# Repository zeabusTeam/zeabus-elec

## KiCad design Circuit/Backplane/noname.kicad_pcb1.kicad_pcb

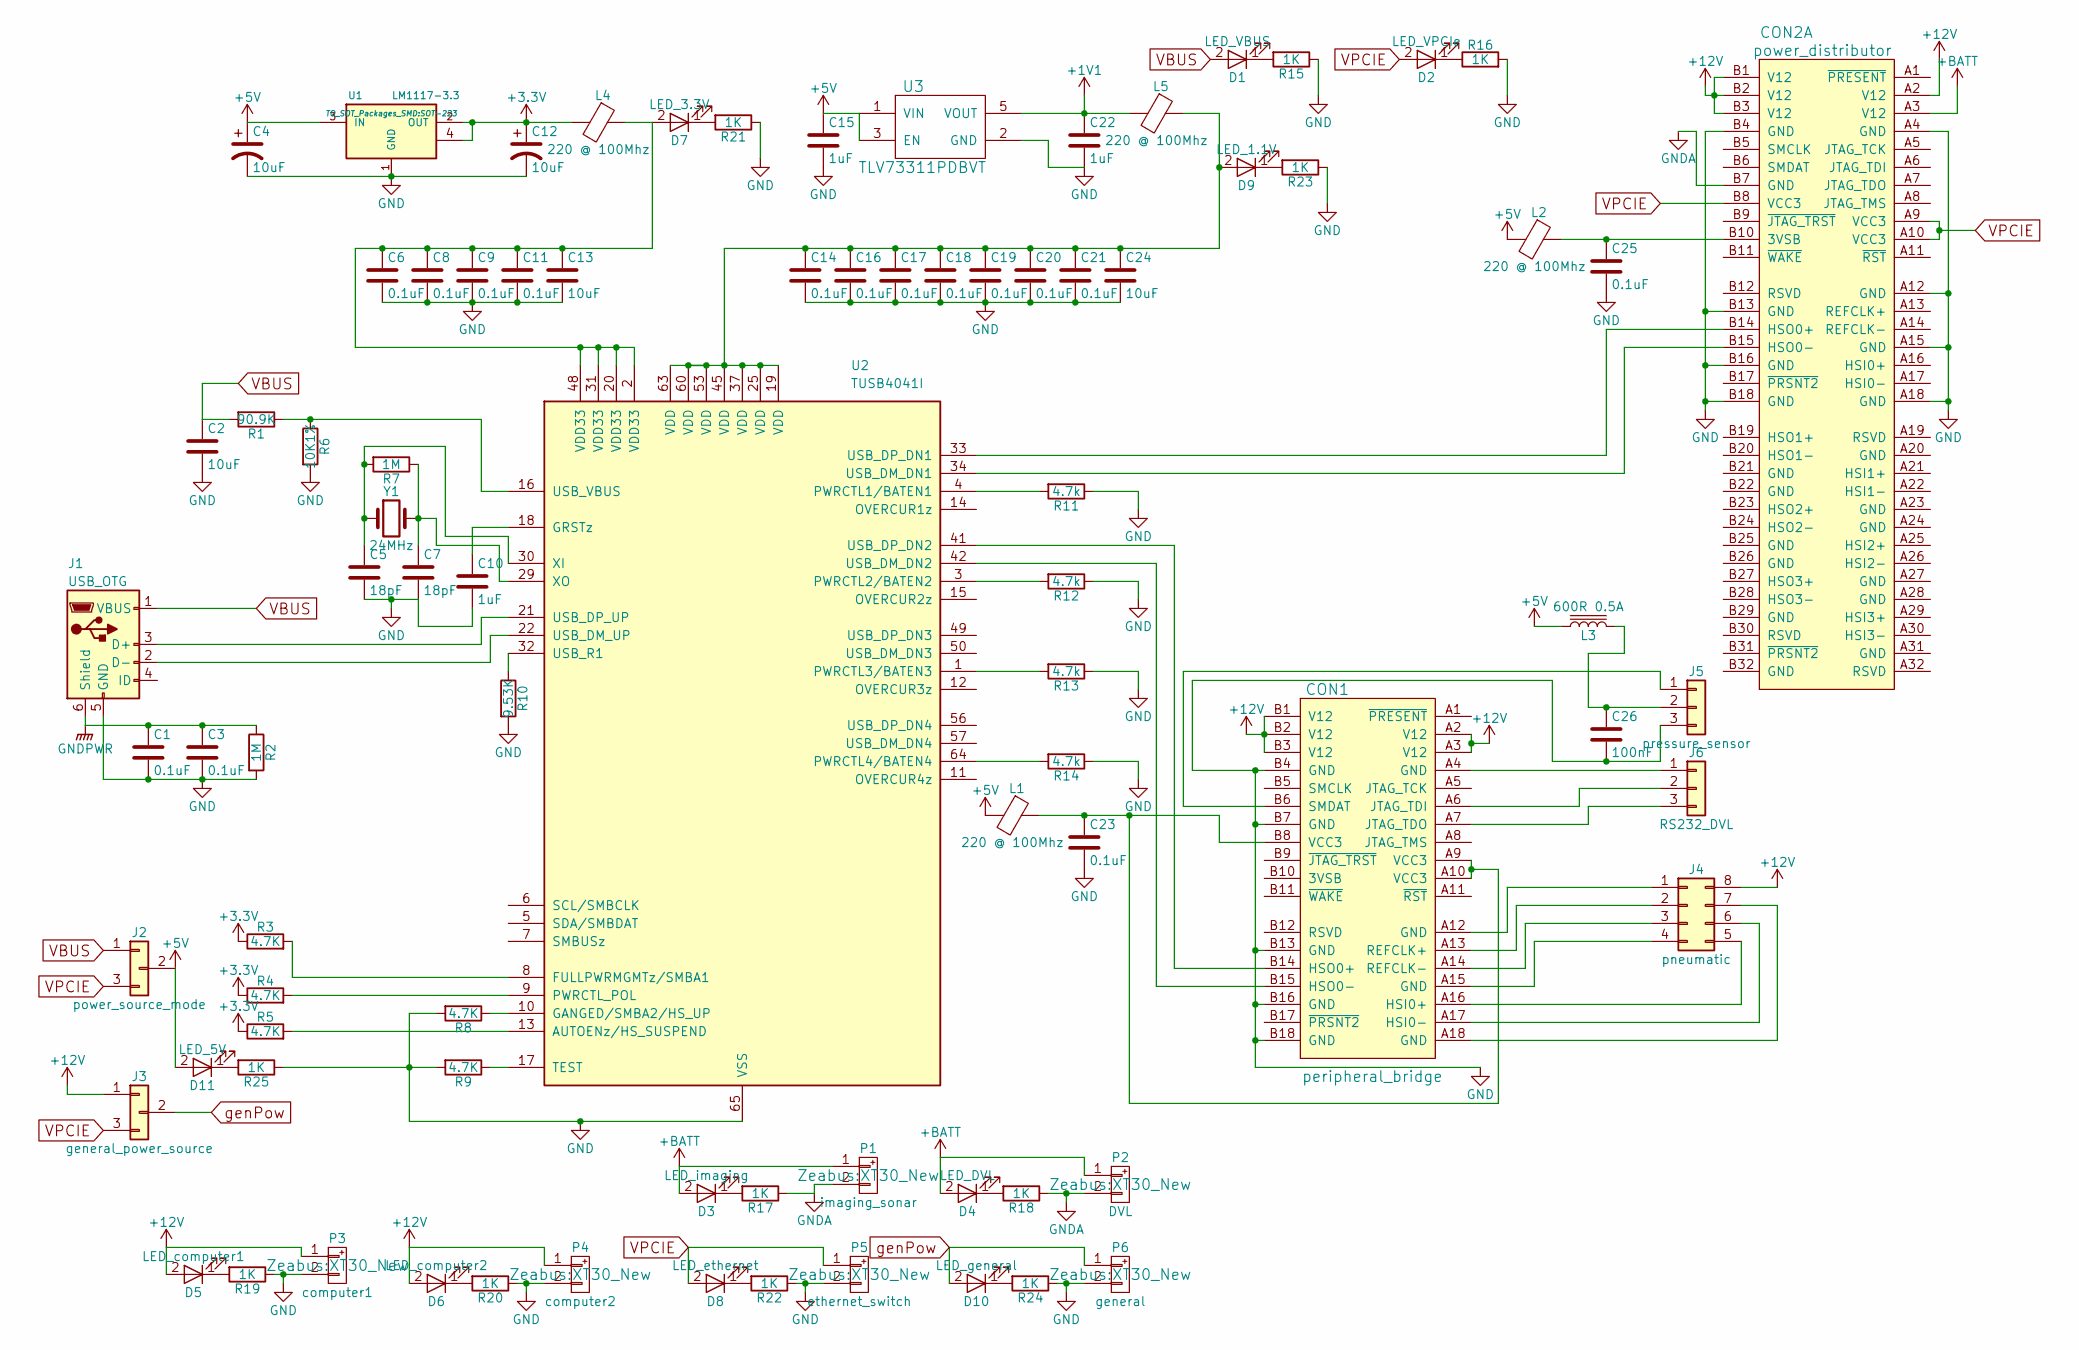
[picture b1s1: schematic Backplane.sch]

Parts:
C1, C3, C6, C8, C9, C11, C14, C16, C17, C18, C19, C20, C21, C23, C25: 0.1uF; C_0603_HandSoldering
C2, C4, C12, C13, C24: 10uF; C_0603_HandSoldering
C5, C7: 18pF; C_0603_HandSoldering
C10, C15, C22: 1uF; C_0603_HandSoldering
C26: 100nF; C_0603_HandSoldering
CON1: peripheral_bridge; pcie-x1-conn
CON2: power_distributor; pcie-x16-conn
D1: LED_VBUS; LED_0603_HandSoldering
D2: LED_VPCIe; LED_0603_HandSoldering
D3: LED_imaging; LED_0603_HandSoldering
D4: LED_DVL; LED_0603_HandSoldering
D5: LED_computer1; LED_0603_HandSoldering
D6: LED_computer2; LED_0603_HandSoldering
D7: LED_3.3V; LED_0603_HandSoldering
D8: LED_ethernet; LED_0603_HandSoldering
D9: LED_1.1V; LED_0603_HandSoldering
D10: LED_general; LED_0603_HandSoldering
D11: LED_5V; LED_0603_HandSoldering
J1: USB_OTG; USB_Mini-B
J2: power_source_mode; Pin_Header_Straight_1x03_Pitch2.54mm
J3: general_power_source; Pin_Header_Straight_1x03_Pitch2.54mm
J4: pneumatic; Pin_Header_Straight_2x04
J5: pressure_sensor; 70543-0002
J6: RS232_DVL; 70543-0002
L1, L2, L4, L5: 220 @ 100Mhz; C_0603_HandSoldering
L3: 600R 0.5A; C_0805_HandSoldering
P1: imaging_sonar; XT30_New
P2: DVL; XT30_New
P3: computer1; XT30_New
P4: computer2; XT30_New
P5: ethernet_switch; XT30_New
P6: general; XT30_New
R1: 90.9K; R_0603_HandSoldering
R2, R7: 1M; R_0603_HandSoldering
R3, R4, R5, R8, R9: 4.7K; R_0603_HandSoldering
R6: 10K1%; R_0603_HandSoldering
R10: 9.53K; R_0603_HandSoldering
R11, R12, R13, R14: 4.7k; R_0603_HandSoldering
R15, R16, R17, R18, R19, R20, R21, R22, R23, R24, R25: 1K; R_0603_HandSoldering
U1: LM1117-3.3; SOT-223
U2: TUSB4041I; HTQFP-64-1EP_10x10mm_Pitch0.5mm_ThermalPad
U3: TLV73311PDBVT; SOT-23-5_HandSoldering
Y1: 24MHz; Crystal_SMD_Abracon_ABM3-2pin_5.0x3.2mm_HandSoldering

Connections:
+1V1: C22.1, L5.2, U3.5 (VOUT)
+3V3: C12.1, L4.2, R3.1, R4.1, R5.1, U1.2 (OUT), U1.4
+5V: C4.1, C15.1, D11.2 (A), J2.2, L1.2, L2.2, L3.1, U1.3 (IN), U3.1 (VIN), U3.3 (EN)
+12V: CON1.A2 (V12), CON1.A3 (V12), CON1.B1 (V12), CON1.B2 (V12), CON1.B3 (V12), CON2.A2 (V12), CON2.B1 (V12), CON2.B2 (V12), CON2.B3 (V12), D5.2 (A), D6.2 (A), J3.1, J4.8, P3.1, P4.1
+BATT: CON2.A3 (V12), D3.2 (A), D4.2 (A), P1.1, P2.1
GND: C1.2, C2.2, C3.2, C4.2, C5.2, C6.2, C7.2, C8.2, C9.2, C10.2, C11.2, C12.2, C13.2, C14.2, C15.2, C16.2, C17.2, C18.2, C19.2, C20.2, C21.2, C22.2, C23.2, C24.2, C25.2, C26.2, CON1.B4 (GND), CON1.B7 (GND), CON1.B13 (GND), CON1.B16 (GND), CON1.B18 (GND), CON2.A4 (GND), CON2.A12 (GND), CON2.A15 (GND), CON2.A18 (GND), CON2.B4 (GND), CON2.B13 (GND), CON2.B16 (GND), CON2.B18 (GND), J1.5 (GND), J5.3, P3.2, P4.2, P5.2, P6.2, R2.2, R6.2, R8.2, R9.2, R10.2, R11.1, R12.1, R13.1, R14.1, R15.1, R16.2, R19.1, R20.1, R21.1, R22.1, R23.1, R24.1, R25.1, U1.1 (GND), U2.47 (RSVD), U2.65 (VSS), U3.2 (GND)
GNDA: CON2.B7 (GND), P1.2, P2.2, R17.1, R18.1
GNDPWR: C1.1, C3.1, J1.6 (Shield), R2.1
unnamed: C5.1, R7.2, U2.30 (XI), Y1.1
unnamed: C7.1, R7.1, U2.29 (XO), Y1.2
unnamed: C10.1, U2.18 (GRSTz)
unnamed: C6.1, C8.1, C9.1, C11.1, C13.1, D7.2 (A), L4.1, U2.2 (VDD33), U2.20 (VDD33), U2.31 (VDD33), U2.48 (VDD33)
unnamed: C14.1, C16.1, C17.1, C18.1, C19.1, C20.1, C21.1, C24.1, D9.2 (A), L5.1, U2.19 (VDD), U2.25 (VDD), U2.37 (VDD), U2.45 (VDD), U2.53 (VDD), U2.60 (VDD), U2.63 (VDD)
unnamed: C23.1, CON1.A9 (VCC3), CON1.A10 (VCC3), CON1.B8 (VCC3), L1.1
unnamed: C25.1, CON2.B10 (3VSB), L2.1
unnamed: C26.1, J5.2, L3.2
unnamed: CON1.A4 (GND), J6.1
unnamed: CON1.A6 (JTAG_TDI), J6.2
unnamed: CON1.A7 (JTAG_TDO), J6.3
unnamed: CON1.A12 (GND), J4.1
unnamed: CON1.A13 (REFCLK+), J4.2
unnamed: CON1.A14 (REFCLK-), J4.3
unnamed: CON1.A15 (GND), J4.4
unnamed: CON1.A16 (HSI0+), J4.5
unnamed: CON1.A17 (HSI0-), J4.6
unnamed: CON1.A18 (GND), J4.7
unnamed: CON1.B6 (SMDAT), J5.1
unnamed: CON1.B14 (HSO0+), U2.41 (USB_DP_DN2)
unnamed: CON1.B15 (HSO0-), U2.42 (USB_DM_DN2)
unnamed: CON2.B14 (HSO0+), U2.33 (USB_DP_DN1)
unnamed: CON2.B15 (HSO0-), U2.34 (USB_DM_DN1)
unnamed: D1.1 (K), R15.2
unnamed: D2.1 (K), R16.1
unnamed: D3.1 (K), R17.2
unnamed: D4.1 (K), R18.2
unnamed: D5.1 (K), R19.2
unnamed: D6.1 (K), R20.2
unnamed: D7.1 (K), R21.2
unnamed: D8.1 (K), R22.2
unnamed: D9.1 (K), R23.2
unnamed: D10.1 (K), R24.2
unnamed: D11.1 (K), R25.2
unnamed: J1.2 (D-), U2.22 (USB_DM_UP)
unnamed: J1.3 (D+), U2.21 (USB_DP_UP)
unnamed: R1.1, R6.1, U2.16 (USB_VBUS)
unnamed: R3.2, U2.8 (FULLPWRMGMTz/SMBA1)
unnamed: R4.2, U2.9 (PWRCTL_POL)
unnamed: R5.2, U2.13 (AUTOENz/HS_SUSPEND)
unnamed: R8.1, U2.10 (GANGED/SMBA2/HS_UP)
unnamed: R9.1, U2.17 (TEST)
unnamed: R10.1, U2.32 (USB_R1)
unnamed: R11.2, U2.4 (PWRCTL1/BATEN1)
unnamed: R12.2, U2.3 (PWRCTL2/BATEN2)
unnamed: R13.2, U2.1 (PWRCTL3/BATEN3)
unnamed: R14.2, U2.64 (PWRCTL4/BATEN4)
VBUS: C2.1, D1.2 (A), J1.1 (VBUS), J2.1, R1.2
VPCIE: CON2.A9 (VCC3), CON2.A10 (VCC3), CON2.B8 (VCC3), D2.2 (A), D8.2 (A), J2.3, J3.3, P5.1
genPow: D10.2 (A), J3.2, P6.1

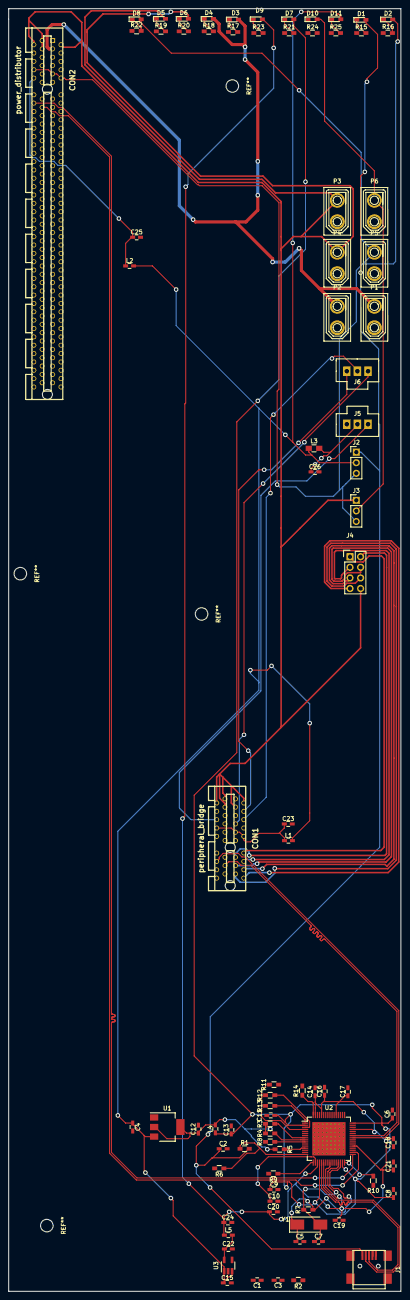
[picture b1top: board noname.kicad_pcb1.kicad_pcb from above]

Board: 2 copper layers, 94.0 x 307.3 mm, 85 parts (0 on the bottom side), 58 nets.

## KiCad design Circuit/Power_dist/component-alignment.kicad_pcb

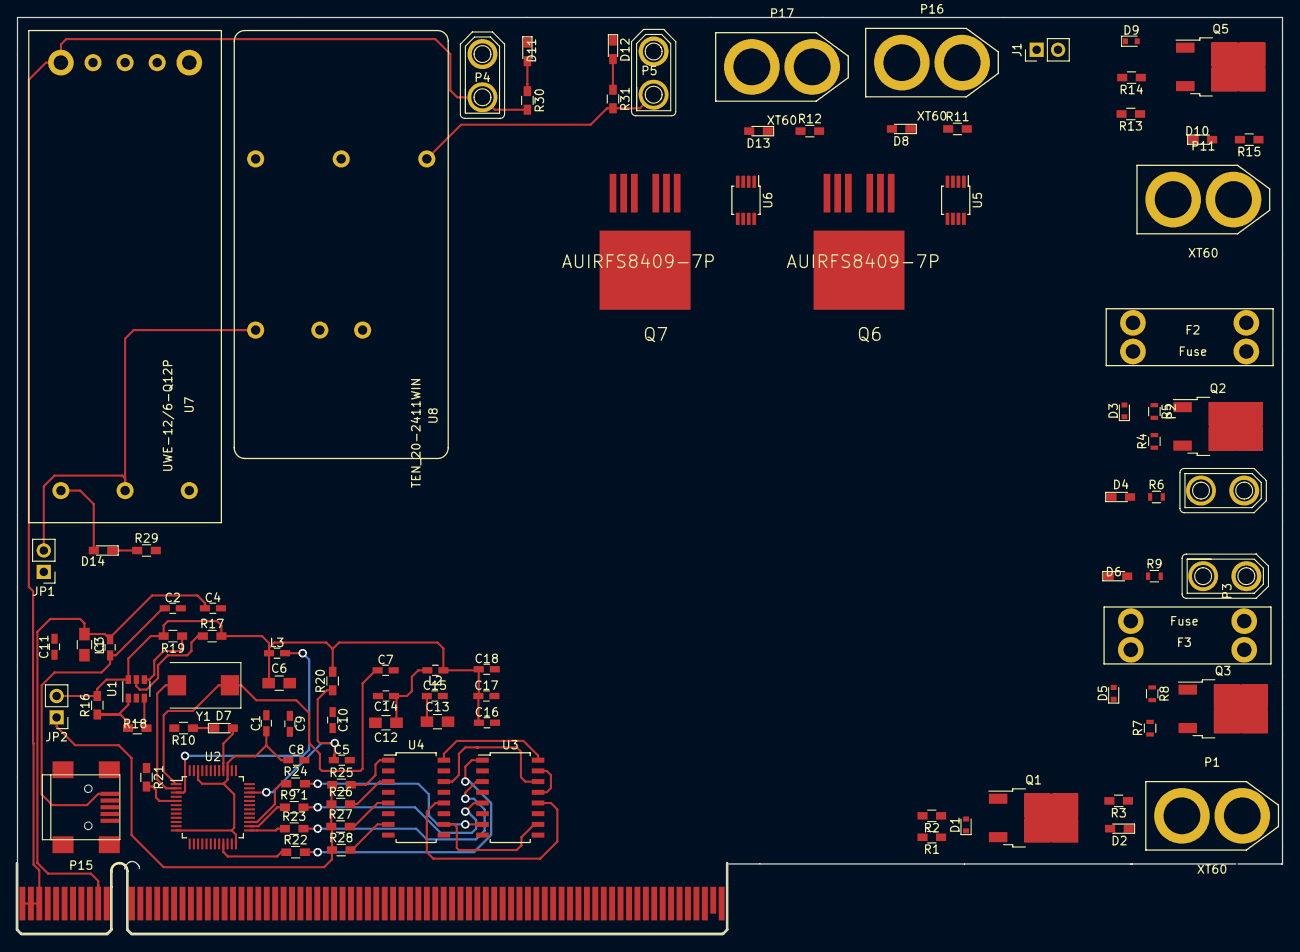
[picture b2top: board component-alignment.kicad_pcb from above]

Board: 2 copper layers, 150.2 x 108.9 mm, 97 parts (0 on the bottom side), 66 nets.

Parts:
C1, C2, C4, C5, C8, C9, C10, C14, C15, C16, C17, C18: 100nF; C_0603_HandSoldering
C3, C6, C12, C13: 4.7uF; C_0805_HandSoldering
C7, C11: 27pF; C_0603_HandSoldering
CON1: Conn-PCIE-x16; pcie-x16-edge
D1, D3, D5, D9: BZX585-C12; D_SOD-523
D2, D4, D6, D7, D8, D10, D13, D14: LED_Small; LED_0603_HandSoldering
D11, D12: Led_Small; LED_0603_HandSoldering
F2, F3: Fuse; FUSE_AUTO
J1: Thruster_Off_Switch; Pin_Header_Straight_1x02_Pitch2.54mm
JP1: Main Switch (N.O.); Pin_Header_Straight_1x02_Pitch2.54mm
JP2: Jumper; Pin_Header_Straight_1x02_Pitch2.54mm
L1, L2, L3: 600R 500mA; C_0603_HandSoldering
P1, P11, P16, P17: XT60
P2, P3, P4, P5: XT30
P15: USB_B; USB_Mini-B
Q1, Q2, Q3, Q5: IPD90P03P4L; TO-252-2
Q6, Q7: AUIRFS8409-7P; D2PAK-7
R1, R3, R11, R12, R13, R15, R16, R17, R19, R20, R29: 10k; R_0603_HandSoldering
R2, R14, R18: 2.2k; R_0603_HandSoldering
R4, R6, R7, R9: 10k; R_0603
R5, R8: 2.2k; R_0603
R9'1, R22, R23, R24, R25, R26, R27, R28: 150; R_0603_HandSoldering
R10, R30, R31: 1k; R_0603_HandSoldering
R21: 12k 1%; R_0603_HandSoldering
U1: 93LC56BT-I/OT; SOT-23-6
U2: FT232H; LQFP-48_7x7mm_Pitch0.5mm
U3, U4: ACPL-247-500E; SO16_4.4x10.3mm_Pitch1.27mm
U5, U6: LTC4357; MSOP-8_3x3mm_Pitch0.65mm
U7: UWE-12/6-Q12P; UWE-xxxx
U8: TEN_20-2411WIN; TEN_20WIN
Y1: 12MHz; Crystal_SMD_FOX_FE-2pin_7.5x5.0mm

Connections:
+3V3: C1.1, C6.1, C8.1, C16.1, C17.1, C18.1, JP2.2, L2.1, L3.1, R16.2, R17.2, R19.2, R20.2, U1.6, U2.12, U2.24, U2.39, U2.46
+5V: CON1.A9, CON1.A10, CON1.B8, P5.1, R31.2, U8.3
+12V: CON1.A2, CON1.B1, CON1.B2, CON1.B3, P4.1, R30.2, U7.8
+BATT: CON1.A3, D1.1, D3.1, D5.1, D9.1, D14.2, Q1.3, Q2.3, Q3.3, Q5.3, Q6.D, Q7.D, R1.1, R4.1, R7.1, R13.1, U5.7, U5.8, U6.7, U6.8, U7.1, U8.1
/Kill_SW: J1.2, U3.13, U3.15
/Power_Controller/D+: P15.3, U2.7
/Power_Controller/D-: P15.2, U2.6
/Power_Controller/SW1_C: R13.2, R14.2, U3.16, U4.16
/Power_Controller/SW2_C: R1.2, R2.2, U3.14, U4.14
/Power_Controller/SW3_C: R4.2, R5.2, U3.12, U4.12
/Power_Controller/SW4_C: R7.2, R8.2, U3.10, U4.10
GND: CON1.B7, D2.1, D4.1, D6.1, D10.1, J1.1, JP1.1, P1.2, P2.2, P3.2, P11.2, P16.2, P17.2, R11.2, R12.2, R29.2, U3.9, U3.11, U4.9, U4.11, U4.13, U4.15, U5.5, U6.5, U7.3, U8.2
GNDD: C1.2, C2.2, C3.2, C4.2, C5.2, C6.2, C7.2, C8.2, C9.1, C10.1, C11.2, C12.2, C13.2, C14.2, C15.2, C16.2, C17.2, C18.2, CON1.B16, P15.5, P15.6, R10.2, R21.1, U1.2, U2.4, U2.9, U2.10, U2.11, U2.22, U2.23, U2.35, U2.36, U2.41, U2.42, U2.47, U2.48, U3.2, U3.4, U3.6, U3.8, U4.2, U4.4, U4.6, U4.8
GNDREF: CON1.A4, CON1.A12, CON1.A15, CON1.A18, CON1.B4, CON1.B13, CON1.B18, D11.1, D12.1, P4.2, P5.2, U7.4, U8.5
unnamed: C2.1, L1.1, P15.1
unnamed: C5.1, R20.1, U2.34
unnamed: C7.1, U2.1, Y1.1
unnamed: C9.2, U2.38
unnamed: C10.2, U2.37
unnamed: C11.1, U2.2, Y1.2
unnamed: C12.1, C14.1, L2.2, U2.8
unnamed: C13.1, C15.1, L3.2, U2.3
unnamed: D1.2, Q1.1, R2.1
unnamed: D2.2, R3.2
unnamed: D3.2, Q2.1, R5.1
unnamed: D4.2, R6.1
unnamed: D5.2, Q3.1, R8.1
unnamed: D6.2, R9.1
unnamed: D7.1, R10.1
unnamed: D8.1, R11.1
unnamed: D8.2, P16.1, Q6.S, U5.1
unnamed: D9.2, Q5.1, R14.1
unnamed: D10.2, R15.2
unnamed: D11.2, R30.1
unnamed: D12.2, R31.1
unnamed: D13.1, R12.1
unnamed: D13.2, P17.1, Q7.S, U6.1
unnamed: D14.1, R29.1
unnamed: F2.1, Q2.2
unnamed: F2.2, P2.1, R6.2
unnamed: F3.1, Q3.2
unnamed: F3.2, P3.1, R9.2
unnamed: JP1.2, U7.2, U8.6
unnamed: JP2.1, R25.1, R26.1, R27.1, R28.1
unnamed: P1.1, Q1.2, R3.1
unnamed: P11.1, Q5.2, R15.1
unnamed: Q6.G, U5.4
unnamed: Q7.G, U6.4
unnamed: R9'1.1, U2.26
unnamed: R9'1.2, U3.5
unnamed: R16.1, R18.1, U1.1
unnamed: R17.1, U1.5, U2.45
unnamed: R18.2, U1.3, U2.43
unnamed: R19.1, U1.4, U2.44
unnamed: R21.2, U2.5
unnamed: R22.1, U2.21
unnamed: R22.2, U3.1
unnamed: R23.1, U2.25
unnamed: R23.2, U3.3
unnamed: R24.1, U2.27
unnamed: R24.2, U3.7
unnamed: R25.2, U4.1
unnamed: R26.2, U4.3
unnamed: R27.2, U4.5
unnamed: R28.2, U4.7
VBUS: C3.1, C4.1, CON1.B10, D7.2, L1.2, U2.40
